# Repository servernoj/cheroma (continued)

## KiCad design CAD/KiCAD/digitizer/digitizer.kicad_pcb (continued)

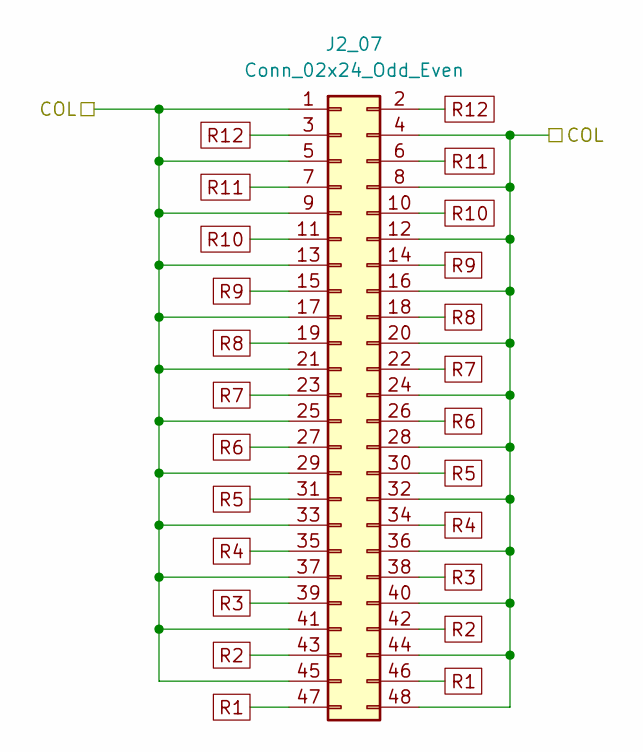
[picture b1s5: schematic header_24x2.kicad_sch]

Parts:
J2_07: Conn_02x24_Odd_Even; PinHeader_2x24_P2.54mm_Vertical

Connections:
C7: J2_07.1, J2_07.4, J2_07.5, J2_07.8, J2_07.9, J2_07.12, J2_07.13, J2_07.16, J2_07.17, J2_07.20, J2_07.21, J2_07.24, J2_07.25, J2_07.28, J2_07.29, J2_07.32, J2_07.33, J2_07.36, J2_07.37, J2_07.40, J2_07.41, J2_07.44, J2_07.45, J2_07.48; also elsewhere on the board
R1: J2_07.46, J2_07.47; also elsewhere on the board
R2: J2_07.42, J2_07.43; also elsewhere on the board
R3: J2_07.38, J2_07.39; also elsewhere on the board
R4: J2_07.34, J2_07.35; also elsewhere on the board
R5: J2_07.30, J2_07.31; also elsewhere on the board
R6: J2_07.26, J2_07.27; also elsewhere on the board
R7: J2_07.22, J2_07.23; also elsewhere on the board
R8: J2_07.18, J2_07.19; also elsewhere on the board
R9: J2_07.14, J2_07.15; also elsewhere on the board
R10: J2_07.10, J2_07.11; also elsewhere on the board
R11: J2_07.6, J2_07.7; also elsewhere on the board
R12: J2_07.2, J2_07.3; also elsewhere on the board

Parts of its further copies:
J2_01, J2_02, J2_03, J2_04, J2_05, J2_06, J2_08, J2_09, J2_10, J2_11, J2_12, J2_13, J2_14, J2_15, J2_16, J2_17, J2_18, J2_19, J2_20, J2_21, J2_22, J2_23, J2_24, J2_25, J2_26, J2_27, J2_28, J2_29, J2_30, J2_31, J2_32: Conn_02x24_Odd_Even; PinHeader_2x24_P2.54mm_Vertical

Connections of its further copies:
C1: J2_01.1, J2_01.4, J2_01.5, J2_01.8, J2_01.9, J2_01.12, J2_01.13, J2_01.16, J2_01.17, J2_01.20, J2_01.21, J2_01.24, J2_01.25, J2_01.28, J2_01.29, J2_01.32, J2_01.33, J2_01.36, J2_01.37, J2_01.40, J2_01.41, J2_01.44, J2_01.45, J2_01.48; also elsewhere on the board
C2: J2_02.1, J2_02.4, J2_02.5, J2_02.8, J2_02.9, J2_02.12, J2_02.13, J2_02.16, J2_02.17, J2_02.20, J2_02.21, J2_02.24, J2_02.25, J2_02.28, J2_02.29, J2_02.32, J2_02.33, J2_02.36, J2_02.37, J2_02.40, J2_02.41, J2_02.44, J2_02.45, J2_02.48; also elsewhere on the board
C3: J2_03.1, J2_03.4, J2_03.5, J2_03.8, J2_03.9, J2_03.12, J2_03.13, J2_03.16, J2_03.17, J2_03.20, J2_03.21, J2_03.24, J2_03.25, J2_03.28, J2_03.29, J2_03.32, J2_03.33, J2_03.36, J2_03.37, J2_03.40, J2_03.41, J2_03.44, J2_03.45, J2_03.48; also elsewhere on the board
C4: J2_04.1, J2_04.4, J2_04.5, J2_04.8, J2_04.9, J2_04.12, J2_04.13, J2_04.16, J2_04.17, J2_04.20, J2_04.21, J2_04.24, J2_04.25, J2_04.28, J2_04.29, J2_04.32, J2_04.33, J2_04.36, J2_04.37, J2_04.40, J2_04.41, J2_04.44, J2_04.45, J2_04.48; also elsewhere on the board
C5: J2_05.1, J2_05.4, J2_05.5, J2_05.8, J2_05.9, J2_05.12, J2_05.13, J2_05.16, J2_05.17, J2_05.20, J2_05.21, J2_05.24, J2_05.25, J2_05.28, J2_05.29, J2_05.32, J2_05.33, J2_05.36, J2_05.37, J2_05.40, J2_05.41, J2_05.44, J2_05.45, J2_05.48; also elsewhere on the board
C6: J2_06.1, J2_06.4, J2_06.5, J2_06.8, J2_06.9, J2_06.12, J2_06.13, J2_06.16, J2_06.17, J2_06.20, J2_06.21, J2_06.24, J2_06.25, J2_06.28, J2_06.29, J2_06.32, J2_06.33, J2_06.36, J2_06.37, J2_06.40, J2_06.41, J2_06.44, J2_06.45, J2_06.48; also elsewhere on the board
C8: J2_08.1, J2_08.4, J2_08.5, J2_08.8, J2_08.9, J2_08.12, J2_08.13, J2_08.16, J2_08.17, J2_08.20, J2_08.21, J2_08.24, J2_08.25, J2_08.28, J2_08.29, J2_08.32, J2_08.33, J2_08.36, J2_08.37, J2_08.40, J2_08.41, J2_08.44, J2_08.45, J2_08.48; also elsewhere on the board
C9: J2_09.1, J2_09.4, J2_09.5, J2_09.8, J2_09.9, J2_09.12, J2_09.13, J2_09.16, J2_09.17, J2_09.20, J2_09.21, J2_09.24, J2_09.25, J2_09.28, J2_09.29, J2_09.32, J2_09.33, J2_09.36, J2_09.37, J2_09.40, J2_09.41, J2_09.44, J2_09.45, J2_09.48; also elsewhere on the board
C10: J2_10.1, J2_10.4, J2_10.5, J2_10.8, J2_10.9, J2_10.12, J2_10.13, J2_10.16, J2_10.17, J2_10.20, J2_10.21, J2_10.24, J2_10.25, J2_10.28, J2_10.29, J2_10.32, J2_10.33, J2_10.36, J2_10.37, J2_10.40, J2_10.41, J2_10.44, J2_10.45, J2_10.48; also elsewhere on the board
C11: J2_11.1, J2_11.4, J2_11.5, J2_11.8, J2_11.9, J2_11.12, J2_11.13, J2_11.16, J2_11.17, J2_11.20, J2_11.21, J2_11.24, J2_11.25, J2_11.28, J2_11.29, J2_11.32, J2_11.33, J2_11.36, J2_11.37, J2_11.40, J2_11.41, J2_11.44, J2_11.45, J2_11.48; also elsewhere on the board
C12: J2_12.1, J2_12.4, J2_12.5, J2_12.8, J2_12.9, J2_12.12, J2_12.13, J2_12.16, J2_12.17, J2_12.20, J2_12.21, J2_12.24, J2_12.25, J2_12.28, J2_12.29, J2_12.32, J2_12.33, J2_12.36, J2_12.37, J2_12.40, J2_12.41, J2_12.44, J2_12.45, J2_12.48; also elsewhere on the board
C13: J2_13.1, J2_13.4, J2_13.5, J2_13.8, J2_13.9, J2_13.12, J2_13.13, J2_13.16, J2_13.17, J2_13.20, J2_13.21, J2_13.24, J2_13.25, J2_13.28, J2_13.29, J2_13.32, J2_13.33, J2_13.36, J2_13.37, J2_13.40, J2_13.41, J2_13.44, J2_13.45, J2_13.48; also elsewhere on the board
C14: J2_14.1, J2_14.4, J2_14.5, J2_14.8, J2_14.9, J2_14.12, J2_14.13, J2_14.16, J2_14.17, J2_14.20, J2_14.21, J2_14.24, J2_14.25, J2_14.28, J2_14.29, J2_14.32, J2_14.33, J2_14.36, J2_14.37, J2_14.40, J2_14.41, J2_14.44, J2_14.45, J2_14.48; also elsewhere on the board
C15: J2_15.1, J2_15.4, J2_15.5, J2_15.8, J2_15.9, J2_15.12, J2_15.13, J2_15.16, J2_15.17, J2_15.20, J2_15.21, J2_15.24, J2_15.25, J2_15.28, J2_15.29, J2_15.32, J2_15.33, J2_15.36, J2_15.37, J2_15.40, J2_15.41, J2_15.44, J2_15.45, J2_15.48; also elsewhere on the board
C16: J2_16.1, J2_16.4, J2_16.5, J2_16.8, J2_16.9, J2_16.12, J2_16.13, J2_16.16, J2_16.17, J2_16.20, J2_16.21, J2_16.24, J2_16.25, J2_16.28, J2_16.29, J2_16.32, J2_16.33, J2_16.36, J2_16.37, J2_16.40, J2_16.41, J2_16.44, J2_16.45, J2_16.48; also elsewhere on the board
C17: J2_17.1, J2_17.4, J2_17.5, J2_17.8, J2_17.9, J2_17.12, J2_17.13, J2_17.16, J2_17.17, J2_17.20, J2_17.21, J2_17.24, J2_17.25, J2_17.28, J2_17.29, J2_17.32, J2_17.33, J2_17.36, J2_17.37, J2_17.40, J2_17.41, J2_17.44, J2_17.45, J2_17.48; also elsewhere on the board
C18: J2_18.1, J2_18.4, J2_18.5, J2_18.8, J2_18.9, J2_18.12, J2_18.13, J2_18.16, J2_18.17, J2_18.20, J2_18.21, J2_18.24, J2_18.25, J2_18.28, J2_18.29, J2_18.32, J2_18.33, J2_18.36, J2_18.37, J2_18.40, J2_18.41, J2_18.44, J2_18.45, J2_18.48; also elsewhere on the board
C19: J2_19.1, J2_19.4, J2_19.5, J2_19.8, J2_19.9, J2_19.12, J2_19.13, J2_19.16, J2_19.17, J2_19.20, J2_19.21, J2_19.24, J2_19.25, J2_19.28, J2_19.29, J2_19.32, J2_19.33, J2_19.36, J2_19.37, J2_19.40, J2_19.41, J2_19.44, J2_19.45, J2_19.48; also elsewhere on the board
C20: J2_20.1, J2_20.4, J2_20.5, J2_20.8, J2_20.9, J2_20.12, J2_20.13, J2_20.16, J2_20.17, J2_20.20, J2_20.21, J2_20.24, J2_20.25, J2_20.28, J2_20.29, J2_20.32, J2_20.33, J2_20.36, J2_20.37, J2_20.40, J2_20.41, J2_20.44, J2_20.45, J2_20.48; also elsewhere on the board
C21: J2_21.1, J2_21.4, J2_21.5, J2_21.8, J2_21.9, J2_21.12, J2_21.13, J2_21.16, J2_21.17, J2_21.20, J2_21.21, J2_21.24, J2_21.25, J2_21.28, J2_21.29, J2_21.32, J2_21.33, J2_21.36, J2_21.37, J2_21.40, J2_21.41, J2_21.44, J2_21.45, J2_21.48; also elsewhere on the board
C22: J2_22.1, J2_22.4, J2_22.5, J2_22.8, J2_22.9, J2_22.12, J2_22.13, J2_22.16, J2_22.17, J2_22.20, J2_22.21, J2_22.24, J2_22.25, J2_22.28, J2_22.29, J2_22.32, J2_22.33, J2_22.36, J2_22.37, J2_22.40, J2_22.41, J2_22.44, J2_22.45, J2_22.48; also elsewhere on the board
C23: J2_23.1, J2_23.4, J2_23.5, J2_23.8, J2_23.9, J2_23.12, J2_23.13, J2_23.16, J2_23.17, J2_23.20, J2_23.21, J2_23.24, J2_23.25, J2_23.28, J2_23.29, J2_23.32, J2_23.33, J2_23.36, J2_23.37, J2_23.40, J2_23.41, J2_23.44, J2_23.45, J2_23.48; also elsewhere on the board
C24: J2_24.1, J2_24.4, J2_24.5, J2_24.8, J2_24.9, J2_24.12, J2_24.13, J2_24.16, J2_24.17, J2_24.20, J2_24.21, J2_24.24, J2_24.25, J2_24.28, J2_24.29, J2_24.32, J2_24.33, J2_24.36, J2_24.37, J2_24.40, J2_24.41, J2_24.44, J2_24.45, J2_24.48; also elsewhere on the board
C25: J2_25.1, J2_25.4, J2_25.5, J2_25.8, J2_25.9, J2_25.12, J2_25.13, J2_25.16, J2_25.17, J2_25.20, J2_25.21, J2_25.24, J2_25.25, J2_25.28, J2_25.29, J2_25.32, J2_25.33, J2_25.36, J2_25.37, J2_25.40, J2_25.41, J2_25.44, J2_25.45, J2_25.48; also elsewhere on the board
C26: J2_26.1, J2_26.4, J2_26.5, J2_26.8, J2_26.9, J2_26.12, J2_26.13, J2_26.16, J2_26.17, J2_26.20, J2_26.21, J2_26.24, J2_26.25, J2_26.28, J2_26.29, J2_26.32, J2_26.33, J2_26.36, J2_26.37, J2_26.40, J2_26.41, J2_26.44, J2_26.45, J2_26.48; also elsewhere on the board
C27: J2_27.1, J2_27.4, J2_27.5, J2_27.8, J2_27.9, J2_27.12, J2_27.13, J2_27.16, J2_27.17, J2_27.20, J2_27.21, J2_27.24, J2_27.25, J2_27.28, J2_27.29, J2_27.32, J2_27.33, J2_27.36, J2_27.37, J2_27.40, J2_27.41, J2_27.44, J2_27.45, J2_27.48; also elsewhere on the board
C28: J2_28.1, J2_28.4, J2_28.5, J2_28.8, J2_28.9, J2_28.12, J2_28.13, J2_28.16, J2_28.17, J2_28.20, J2_28.21, J2_28.24, J2_28.25, J2_28.28, J2_28.29, J2_28.32, J2_28.33, J2_28.36, J2_28.37, J2_28.40, J2_28.41, J2_28.44, J2_28.45, J2_28.48; also elsewhere on the board
C29: J2_29.1, J2_29.4, J2_29.5, J2_29.8, J2_29.9, J2_29.12, J2_29.13, J2_29.16, J2_29.17, J2_29.20, J2_29.21, J2_29.24, J2_29.25, J2_29.28, J2_29.29, J2_29.32, J2_29.33, J2_29.36, J2_29.37, J2_29.40, J2_29.41, J2_29.44, J2_29.45, J2_29.48; also elsewhere on the board
C30: J2_30.1, J2_30.4, J2_30.5, J2_30.8, J2_30.9, J2_30.12, J2_30.13, J2_30.16, J2_30.17, J2_30.20, J2_30.21, J2_30.24, J2_30.25, J2_30.28, J2_30.29, J2_30.32, J2_30.33, J2_30.36, J2_30.37, J2_30.40, J2_30.41, J2_30.44, J2_30.45, J2_30.48; also elsewhere on the board
C31: J2_31.1, J2_31.4, J2_31.5, J2_31.8, J2_31.9, J2_31.12, J2_31.13, J2_31.16, J2_31.17, J2_31.20, J2_31.21, J2_31.24, J2_31.25, J2_31.28, J2_31.29, J2_31.32, J2_31.33, J2_31.36, J2_31.37, J2_31.40, J2_31.41, J2_31.44, J2_31.45, J2_31.48; also elsewhere on the board
C32: J2_32.1, J2_32.4, J2_32.5, J2_32.8, J2_32.9, J2_32.12, J2_32.13, J2_32.16, J2_32.17, J2_32.20, J2_32.21, J2_32.24, J2_32.25, J2_32.28, J2_32.29, J2_32.32, J2_32.33, J2_32.36, J2_32.37, J2_32.40, J2_32.41, J2_32.44, J2_32.45, J2_32.48; also elsewhere on the board
R1: J2_01.46, J2_01.47, J2_02.46, J2_02.47, J2_03.46, J2_03.47, J2_04.46, J2_04.47, J2_05.46, J2_05.47, J2_06.46, J2_06.47, J2_08.46, J2_08.47, J2_09.46, J2_09.47, J2_10.46, J2_10.47, J2_11.46, J2_11.47, J2_12.46, J2_12.47, J2_13.46, J2_13.47, J2_14.46, J2_14.47, J2_15.46, J2_15.47, J2_16.46, J2_16.47, J2_17.46, J2_17.47, J2_18.46, J2_18.47, J2_19.46, J2_19.47, J2_20.46, J2_20.47, J2_21.46, J2_21.47, J2_22.46, J2_22.47, J2_23.46, J2_23.47, J2_24.46, J2_24.47, J2_25.46, J2_25.47, J2_26.46, J2_26.47, J2_27.46, J2_27.47, J2_28.46, J2_28.47, J2_29.46, J2_29.47, J2_30.46, J2_30.47, J2_31.46, J2_31.47, J2_32.46, J2_32.47; also elsewhere on the board
R2: J2_01.42, J2_01.43, J2_02.42, J2_02.43, J2_03.42, J2_03.43, J2_04.42, J2_04.43, J2_05.42, J2_05.43, J2_06.42, J2_06.43, J2_08.42, J2_08.43, J2_09.42, J2_09.43, J2_10.42, J2_10.43, J2_11.42, J2_11.43, J2_12.42, J2_12.43, J2_13.42, J2_13.43, J2_14.42, J2_14.43, J2_15.42, J2_15.43, J2_16.42, J2_16.43, J2_17.42, J2_17.43, J2_18.42, J2_18.43, J2_19.42, J2_19.43, J2_20.42, J2_20.43, J2_21.42, J2_21.43, J2_22.42, J2_22.43, J2_23.42, J2_23.43, J2_24.42, J2_24.43, J2_25.42, J2_25.43, J2_26.42, J2_26.43, J2_27.42, J2_27.43, J2_28.42, J2_28.43, J2_29.42, J2_29.43, J2_30.42, J2_30.43, J2_31.42, J2_31.43, J2_32.42, J2_32.43; also elsewhere on the board
R3: J2_01.38, J2_01.39, J2_02.38, J2_02.39, J2_03.38, J2_03.39, J2_04.38, J2_04.39, J2_05.38, J2_05.39, J2_06.38, J2_06.39, J2_08.38, J2_08.39, J2_09.38, J2_09.39, J2_10.38, J2_10.39, J2_11.38, J2_11.39, J2_12.38, J2_12.39, J2_13.38, J2_13.39, J2_14.38, J2_14.39, J2_15.38, J2_15.39, J2_16.38, J2_16.39, J2_17.38, J2_17.39, J2_18.38, J2_18.39, J2_19.38, J2_19.39, J2_20.38, J2_20.39, J2_21.38, J2_21.39, J2_22.38, J2_22.39, J2_23.38, J2_23.39, J2_24.38, J2_24.39, J2_25.38, J2_25.39, J2_26.38, J2_26.39, J2_27.38, J2_27.39, J2_28.38, J2_28.39, J2_29.38, J2_29.39, J2_30.38, J2_30.39, J2_31.38, J2_31.39, J2_32.38, J2_32.39; also elsewhere on the board
R4: J2_01.34, J2_01.35, J2_02.34, J2_02.35, J2_03.34, J2_03.35, J2_04.34, J2_04.35, J2_05.34, J2_05.35, J2_06.34, J2_06.35, J2_08.34, J2_08.35, J2_09.34, J2_09.35, J2_10.34, J2_10.35, J2_11.34, J2_11.35, J2_12.34, J2_12.35, J2_13.34, J2_13.35, J2_14.34, J2_14.35, J2_15.34, J2_15.35, J2_16.34, J2_16.35, J2_17.34, J2_17.35, J2_18.34, J2_18.35, J2_19.34, J2_19.35, J2_20.34, J2_20.35, J2_21.34, J2_21.35, J2_22.34, J2_22.35, J2_23.34, J2_23.35, J2_24.34, J2_24.35, J2_25.34, J2_25.35, J2_26.34, J2_26.35, J2_27.34, J2_27.35, J2_28.34, J2_28.35, J2_29.34, J2_29.35, J2_30.34, J2_30.35, J2_31.34, J2_31.35, J2_32.34, J2_32.35; also elsewhere on the board
R5: J2_01.30, J2_01.31, J2_02.30, J2_02.31, J2_03.30, J2_03.31, J2_04.30, J2_04.31, J2_05.30, J2_05.31, J2_06.30, J2_06.31, J2_08.30, J2_08.31, J2_09.30, J2_09.31, J2_10.30, J2_10.31, J2_11.30, J2_11.31, J2_12.30, J2_12.31, J2_13.30, J2_13.31, J2_14.30, J2_14.31, J2_15.30, J2_15.31, J2_16.30, J2_16.31, J2_17.30, J2_17.31, J2_18.30, J2_18.31, J2_19.30, J2_19.31, J2_20.30, J2_20.31, J2_21.30, J2_21.31, J2_22.30, J2_22.31, J2_23.30, J2_23.31, J2_24.30, J2_24.31, J2_25.30, J2_25.31, J2_26.30, J2_26.31, J2_27.30, J2_27.31, J2_28.30, J2_28.31, J2_29.30, J2_29.31, J2_30.30, J2_30.31, J2_31.30, J2_31.31, J2_32.30, J2_32.31; also elsewhere on the board
R6: J2_01.26, J2_01.27, J2_02.26, J2_02.27, J2_03.26, J2_03.27, J2_04.26, J2_04.27, J2_05.26, J2_05.27, J2_06.26, J2_06.27, J2_08.26, J2_08.27, J2_09.26, J2_09.27, J2_10.26, J2_10.27, J2_11.26, J2_11.27, J2_12.26, J2_12.27, J2_13.26, J2_13.27, J2_14.26, J2_14.27, J2_15.26, J2_15.27, J2_16.26, J2_16.27, J2_17.26, J2_17.27, J2_18.26, J2_18.27, J2_19.26, J2_19.27, J2_20.26, J2_20.27, J2_21.26, J2_21.27, J2_22.26, J2_22.27, J2_23.26, J2_23.27, J2_24.26, J2_24.27, J2_25.26, J2_25.27, J2_26.26, J2_26.27, J2_27.26, J2_27.27, J2_28.26, J2_28.27, J2_29.26, J2_29.27, J2_30.26, J2_30.27, J2_31.26, J2_31.27, J2_32.26, J2_32.27; also elsewhere on the board
R7: J2_01.22, J2_01.23, J2_02.22, J2_02.23, J2_03.22, J2_03.23, J2_04.22, J2_04.23, J2_05.22, J2_05.23, J2_06.22, J2_06.23, J2_08.22, J2_08.23, J2_09.22, J2_09.23, J2_10.22, J2_10.23, J2_11.22, J2_11.23, J2_12.22, J2_12.23, J2_13.22, J2_13.23, J2_14.22, J2_14.23, J2_15.22, J2_15.23, J2_16.22, J2_16.23, J2_17.22, J2_17.23, J2_18.22, J2_18.23, J2_19.22, J2_19.23, J2_20.22, J2_20.23, J2_21.22, J2_21.23, J2_22.22, J2_22.23, J2_23.22, J2_23.23, J2_24.22, J2_24.23, J2_25.22, J2_25.23, J2_26.22, J2_26.23, J2_27.22, J2_27.23, J2_28.22, J2_28.23, J2_29.22, J2_29.23, J2_30.22, J2_30.23, J2_31.22, J2_31.23, J2_32.22, J2_32.23; also elsewhere on the board
R8: J2_01.18, J2_01.19, J2_02.18, J2_02.19, J2_03.18, J2_03.19, J2_04.18, J2_04.19, J2_05.18, J2_05.19, J2_06.18, J2_06.19, J2_08.18, J2_08.19, J2_09.18, J2_09.19, J2_10.18, J2_10.19, J2_11.18, J2_11.19, J2_12.18, J2_12.19, J2_13.18, J2_13.19, J2_14.18, J2_14.19, J2_15.18, J2_15.19, J2_16.18, J2_16.19, J2_17.18, J2_17.19, J2_18.18, J2_18.19, J2_19.18, J2_19.19, J2_20.18, J2_20.19, J2_21.18, J2_21.19, J2_22.18, J2_22.19, J2_23.18, J2_23.19, J2_24.18, J2_24.19, J2_25.18, J2_25.19, J2_26.18, J2_26.19, J2_27.18, J2_27.19, J2_28.18, J2_28.19, J2_29.18, J2_29.19, J2_30.18, J2_30.19, J2_31.18, J2_31.19, J2_32.18, J2_32.19; also elsewhere on the board
R9: J2_01.14, J2_01.15, J2_02.14, J2_02.15, J2_03.14, J2_03.15, J2_04.14, J2_04.15, J2_05.14, J2_05.15, J2_06.14, J2_06.15, J2_08.14, J2_08.15, J2_09.14, J2_09.15, J2_10.14, J2_10.15, J2_11.14, J2_11.15, J2_12.14, J2_12.15, J2_13.14, J2_13.15, J2_14.14, J2_14.15, J2_15.14, J2_15.15, J2_16.14, J2_16.15, J2_17.14, J2_17.15, J2_18.14, J2_18.15, J2_19.14, J2_19.15, J2_20.14, J2_20.15, J2_21.14, J2_21.15, J2_22.14, J2_22.15, J2_23.14, J2_23.15, J2_24.14, J2_24.15, J2_25.14, J2_25.15, J2_26.14, J2_26.15, J2_27.14, J2_27.15, J2_28.14, J2_28.15, J2_29.14, J2_29.15, J2_30.14, J2_30.15, J2_31.14, J2_31.15, J2_32.14, J2_32.15; also elsewhere on the board
R10: J2_01.10, J2_01.11, J2_02.10, J2_02.11, J2_03.10, J2_03.11, J2_04.10, J2_04.11, J2_05.10, J2_05.11, J2_06.10, J2_06.11, J2_08.10, J2_08.11, J2_09.10, J2_09.11, J2_10.10, J2_10.11, J2_11.10, J2_11.11, J2_12.10, J2_12.11, J2_13.10, J2_13.11, J2_14.10, J2_14.11, J2_15.10, J2_15.11, J2_16.10, J2_16.11, J2_17.10, J2_17.11, J2_18.10, J2_18.11, J2_19.10, J2_19.11, J2_20.10, J2_20.11, J2_21.10, J2_21.11, J2_22.10, J2_22.11, J2_23.10, J2_23.11, J2_24.10, J2_24.11, J2_25.10, J2_25.11, J2_26.10, J2_26.11, J2_27.10, J2_27.11, J2_28.10, J2_28.11, J2_29.10, J2_29.11, J2_30.10, J2_30.11, J2_31.10, J2_31.11, J2_32.10, J2_32.11; also elsewhere on the board
R11: J2_01.6, J2_01.7, J2_02.6, J2_02.7, J2_03.6, J2_03.7, J2_04.6, J2_04.7, J2_05.6, J2_05.7, J2_06.6, J2_06.7, J2_08.6, J2_08.7, J2_09.6, J2_09.7, J2_10.6, J2_10.7, J2_11.6, J2_11.7, J2_12.6, J2_12.7, J2_13.6, J2_13.7, J2_14.6, J2_14.7, J2_15.6, J2_15.7, J2_16.6, J2_16.7, J2_17.6, J2_17.7, J2_18.6, J2_18.7, J2_19.6, J2_19.7, J2_20.6, J2_20.7, J2_21.6, J2_21.7, J2_22.6, J2_22.7, J2_23.6, J2_23.7, J2_24.6, J2_24.7, J2_25.6, J2_25.7, J2_26.6, J2_26.7, J2_27.6, J2_27.7, J2_28.6, J2_28.7, J2_29.6, J2_29.7, J2_30.6, J2_30.7, J2_31.6, J2_31.7, J2_32.6, J2_32.7; also elsewhere on the board
R12: J2_01.2, J2_01.3, J2_02.2, J2_02.3, J2_03.2, J2_03.3, J2_04.2, J2_04.3, J2_05.2, J2_05.3, J2_06.2, J2_06.3, J2_08.2, J2_08.3, J2_09.2, J2_09.3, J2_10.2, J2_10.3, J2_11.2, J2_11.3, J2_12.2, J2_12.3, J2_13.2, J2_13.3, J2_14.2, J2_14.3, J2_15.2, J2_15.3, J2_16.2, J2_16.3, J2_17.2, J2_17.3, J2_18.2, J2_18.3, J2_19.2, J2_19.3, J2_20.2, J2_20.3, J2_21.2, J2_21.3, J2_22.2, J2_22.3, J2_23.2, J2_23.3, J2_24.2, J2_24.3, J2_25.2, J2_25.3, J2_26.2, J2_26.3, J2_27.2, J2_27.3, J2_28.2, J2_28.3, J2_29.2, J2_29.3, J2_30.2, J2_30.3, J2_31.2, J2_31.3, J2_32.2, J2_32.3; also elsewhere on the board

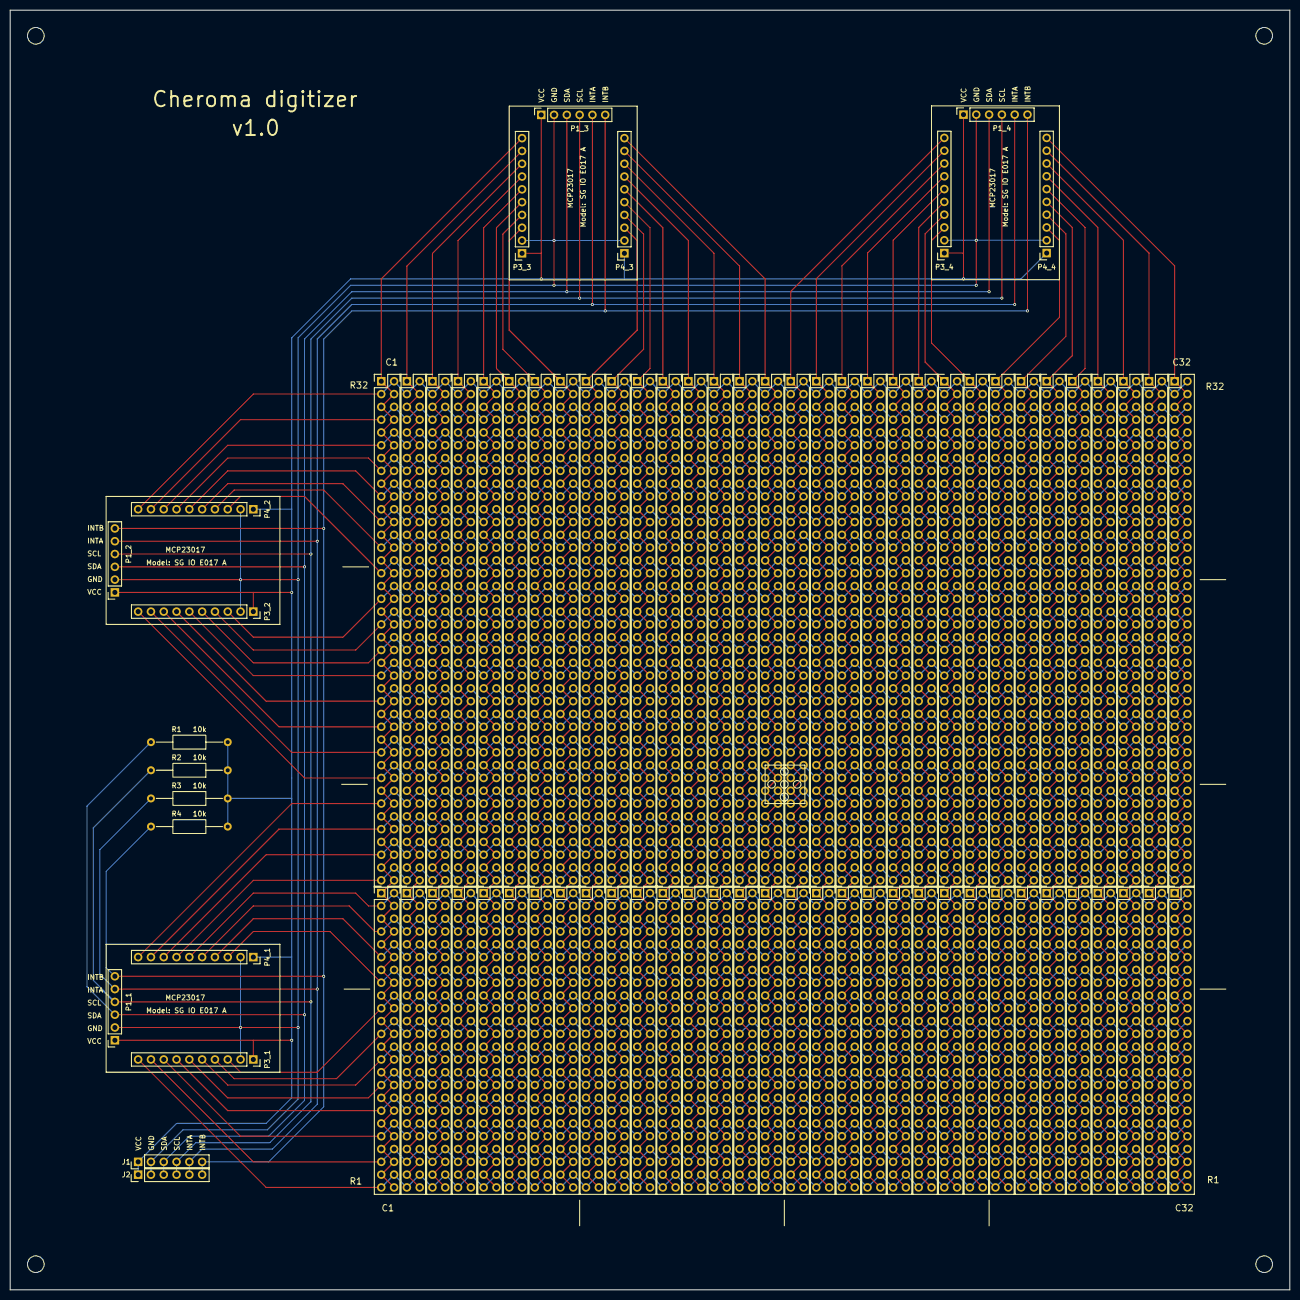
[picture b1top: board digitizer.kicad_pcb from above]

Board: 2 copper layers, 254.0 x 254.0 mm, 82 parts (0 on the bottom side), 70 nets.

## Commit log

2025-12-24 init
2025-12-24 api: add basic servo
2025-12-25 bug fixes
2025-12-25 repo: update README
2025-12-26 api: add cal for 5 servos
2025-12-31 api: experiments
2026-01-05 add 3d models and calibration scripts
2026-01-18 homing and new calibration added
2026-01-19 add path planning
2026-01-20 refactor to use config.json
2026-01-21 FK tested OK
2026-01-21 IK passes smoke testting
2026-01-21 add arm controller
2026-01-21 refactor to exclude numPoints
2026-01-21 update IK to support dX > 0
2026-01-21 add /arm/home-then-to endpoint
2026-01-22 new config (updated lengths)
2026-01-22 fixes
2026-01-22 home at start
2026-01-23 add support for `via` in arm/to endpoint
2026-01-24 introduce correction
2026-01-25 new docs
2026-01-25 smooth motion with easing
2026-01-26 xy fitted
2026-01-26 updated docs to proceed with 6-DOF design
2026-01-27 matlab wip take 1
2026-01-27 matlab code for new IK (6-DOF) works
2026-01-27 update config to list all geom props
2026-01-28 update JS with new FK and IK
2026-01-31 speed tuning
2026-02-01 new fitting
2026-02-07 latest
2026-02-08 adopted basic 4-DOF design (with magnet)
2026-02-11 new calData
2026-02-12 new calPoints (from disassembled arm)
2026-02-13 fitted with registration and ab
2026-02-13 with magnet control
2026-02-15 descent optimization
2026-02-16 add move motion
2026-02-20 new 3d parts
2026-02-21 add handling of SIGINT and SIGTERM
2026-02-22 update README to include new service config
2026-02-22 refactor board/move
2026-02-23 fixes for servo/toPoint
2026-02-23 set PWM freq to 250Hz
2026-02-24 optimization to support 400kHz i2c bus speed
2026-02-24 Optimizations for higher PWM frequency (250Hz) and i2c bus speed (400kHz)
2026-03-01 correction for 4th rank misperfection
2026-03-02 full board fitting
2026-03-03 new calPoints for base servo
2026-03-04 reset config + rearrange CAD files
2026-03-04 add digitizer draft
2026-03-05 add digitizer tracks
2026-03-05 add MCP23017 for rows (no routing)
2026-03-06 one MCP23017 added and routed
2026-03-06 routing wip take 1
2026-03-07 digitizer draft with MCP23017 routing
    Made-with: Cursor
2026-03-07 cleanup
2026-03-08 remove gerber files
2026-03-10 latest CAD files, pre-release
2026-03-10 updated digitizer holder CAD
2026-03-10 cad: add pull-up resistors to interrupt lines
2026-03-10 initial changes for MCP23017 support, wip
2026-03-11 MCP23017: ready to test
2026-03-11 updated onoff dependency
2026-03-11 update pnpm workspace config
2026-03-11 enable pull-up on GPIO 27 during init
2026-03-12 working draft
2026-03-12 docs and polishing
2026-03-12 adopt new version of onoff (v1.0.3-memory_leak_fix)
2026-03-12 bump up version of the forked onoff
2026-03-12 add support for INTF
2026-03-12 adopt v1.0.5 of the onoff fork (patched memory leak)
2026-03-12 split optimized combined read of INTF and INTCAP to make sure that flag is erased
2026-03-12 fix for incorrect offset
2026-03-12 read 6 bytes at capture (INTF, INTCAP, GPIO)
2026-03-13 disable interrupts in the meantime
2026-03-13 digitizer timeline tunning
2026-03-13 rearrange CAD files
2026-03-13 digitizer integration draft take 1
2026-03-14 digitizer casing rev1.1
2026-03-14 digitizer reports bits on target
2026-03-14 update touchDataToDigitizerXY
2026-03-18 freeCAD: add digitizer spacer model
2026-03-18 freecad: update base and spacer designs
2026-03-19 worker for chess.com polling draft
2026-03-19 basic worker setup to poll the game progress (no arm moves)
2026-03-21 refactor to split i2c module from utils
2026-03-21 refactor position reporting
2026-03-21 tunning of interrupt handling
2026-03-23 calibration first test
2026-03-23 implement median filter for calibration
2026-03-23 add arm motion to live game
2026-03-25 cad models for chess pieces
2026-03-28 add hollow pieces
2026-03-28 remove files from the root
2026-03-29 cad: digitizer rev1.2
2026-03-29 cad: update spacer and base digitizer
2026-03-29 calibration: slow down descent and go to preTarget after every touch before going home
2026-03-29 calibration: force rounding to 2 positions
2026-03-29 calibration: apply automatically collected measurement data
2026-03-30 cad: update digitizer to increase manufacturing tolerance
2026-03-31 implement LM fitting in JS (xyzFitting.js)
2026-04-02 cv: added draft integration with OpenCV
2026-04-02 CV: refactor cameras enumeration
2026-04-03 cv: board geometry detection without markers
2026-04-04 cv: board detection wip (aruco, debug)
2026-04-04 working border detection (no aruco)
2026-04-04 cv: persist and reuse calibration data
2026-04-06 updare project readme to include description and video links
2026-04-06 remove CV
2026-04-07 new config
2026-04-07 refactor modules/servo.js
2026-04-07 refactor servo.js
2026-04-07 refactor board.js
2026-04-08 api: refactor to add `arm` module
2026-04-10 CV: script(s) to detect coordinates based on offline image with markers
2026-04-11 add CV from `cv` branch
2026-04-11 fixes to calibration flow
2026-04-12 update xyzFitting (JS) to read config.json directly
2026-04-13 add xy_fitting (matlab)
2026-04-13 latest xy fitting params
2026-04-15 new fitters
2026-04-15 cad: update chess pieces (non-functional)
2026-04-16 back to affine fitter (both XY and Z) and fitted XY coefficients in config.json
2026-04-16 docs: add trilateration math workbook
2026-04-20 make digitizer optional
